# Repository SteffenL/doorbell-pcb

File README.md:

# Doorbell PCB

Prototype design for doorbell hardware.

Related projects:
* https://github.com/SteffenL/doorbell-mcu
* https://github.com/SteffenL/doorbell-app-android
* https://github.com/SteffenL/doorbell-server

Features:

* Plugs into a LOLIN32 development board (Espressif ESP32).
* Battery and USB charging support.
* Buzzer, e.g. for emitting sounds when pressing the button.
* LOLIN32 hack for battery level monitoring.

<div style="clear: both"></div>

<div style="clear: both"></div>

<div style="clear: both"></div>
<p>
  <video style="float: left; width: 640px; height: 360px" src="https://github.com/SteffenL/doorbell-pcb/assets/1543854/65a9893a-05a4-455d-b5d6-bc498b06eb5a"></video>
</p>
<div style="clear: both"></div>

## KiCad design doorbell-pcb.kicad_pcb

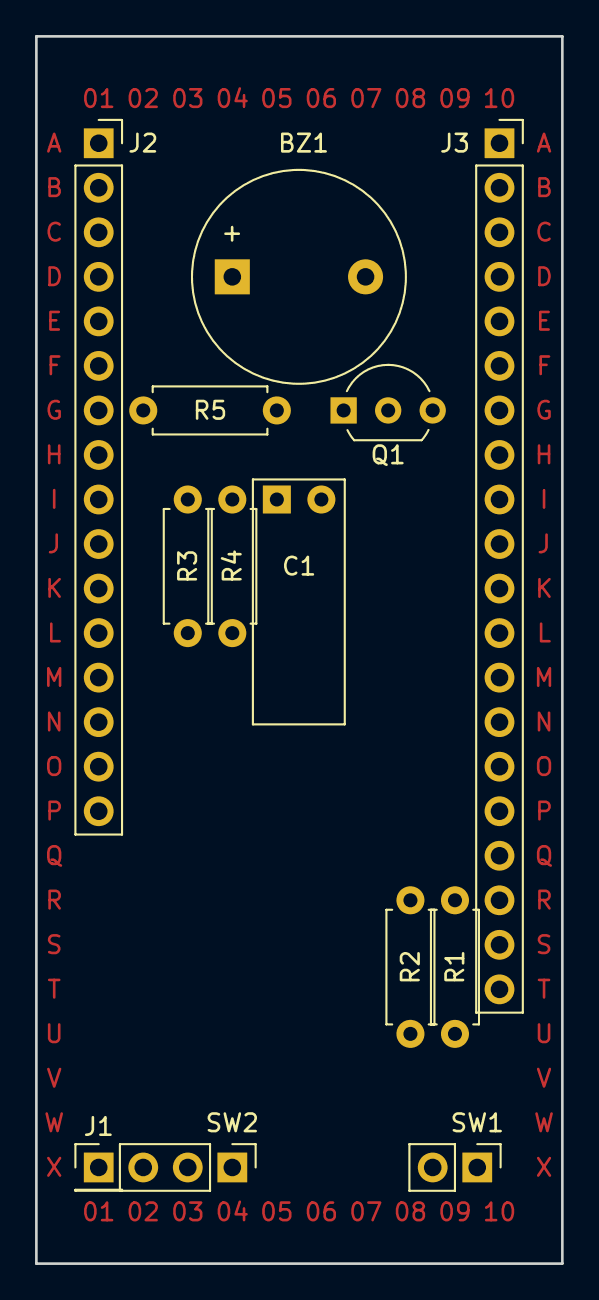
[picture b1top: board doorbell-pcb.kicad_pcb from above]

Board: 2 copper layers, 30.0 x 70.0 mm, 13 parts (0 on the bottom side), 9 nets.

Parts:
BZ1: Buzzer; Buzzer_12x9.5RM7.6
C1: 10u; C_Radial_D5.0mm_H11.0mm_P2.54mm
J1: LDO_IN; PinHeader_1x01_P2.54mm_Vertical
J2: Socket; PinSocket_1x16_P2.54mm_Vertical
J3: Socket; PinSocket_1x20_P2.54mm_Vertical
Q1: 2N2222; TO-92L_Inline_Wide
R1, R2, R3, R4: 100k; R_Axial_DIN0207_L6.3mm_D2.5mm_P7.62mm_Horizontal
R5: 1k; R_Axial_DIN0207_L6.3mm_D2.5mm_P7.62mm_Horizontal
SW1: Ring button; PinHeader_1x02_P2.54mm_Vertical
SW2: F.Reset; PinHeader_1x03_P2.54mm_Vertical

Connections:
+3V3: J2.1, J3.4, J3.13, R2.2, SW1.2
BAT_VREF: C1.1, J2.8, R3.2, R4.1
BUZZER: J2.9, R5.2
FACTORY_RESET: J3.16, R2.1, SW2.1
GND: C1.2, J2.16, J3.1, J3.7, J3.8, J3.18, Q1.3, R1.1, R4.2, SW2.2
unnamed: BZ1.2, Q1.1
unnamed: Q1.2, R5.1
RING: J3.20, R1.2, SW1.1
VIN: BZ1.1, J1.1, R3.1

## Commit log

2024-01-30 Add initial readme
2024-01-30 Add brief project description to readme
2024-01-30 Update video in README
2024-01-30 Update README.md
    Add reference to MCU and Android app projects
2024-01-30 Update README.md
    Add reference to server project.
